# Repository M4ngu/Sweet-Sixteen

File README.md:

# Sweet-Sixteen
Eurorack module based in the [16n faderbank][16n-faderbank/16n]. 

## The following changes were made to the original hardware:

-The PCB layout has been made from scratch, so it's totally different, with 0603 passives instead of 0805.

-A power section has been added to work within the eurorack modular synth format, with diode protection and the option to power the Teensy with an internal 5V LDO or the eurorack 5V rail (selectable with a jumper on the back of the module). The voltage to feed the faders now comes from a dedicated voltage regulator, more stable and precise than most USB voltage sources.

-16 Inputs has been added. A "default voltage" is normalled to the input jacks, so when something is plugged in, that normalization is broken, being the incomming CV attenuated by the fader. This adition makes the module to work also as 16 attenuators, Cv to Midi, Cv to i2C...

-The op-amps circuit has been modiffied, being TL074s for the CV outs and MCP6004s for the circuit that prepares the voltages to be read by the Teensy. In this version the MCP6004 are powered with 3,3V & GND (instead of the original 5V), the rail-to-rail characteristic of those op-amps provides voltage protection to the Teensy. That is specially handy for the CV inputs, as any voltage plugged in, will be limited to 3,3v by the MCP6004s. Another important modification in this part of the circuit is the addition of negative voltage references and that now is a summing inverting gain circuit (for that reason the FLIP option in the firmware is necessary for this version of the hardware, as in the minimum position of the fader the voltage readed by the Teensy will be 3,3V and in the max position it will be 0V). The TL074s are powered by +12V & -12V.

-Four slide switches has been added to swap the voltage reference (1 for every 4 faders, there was no room for 16 switches). The reason is to allow negative voltages to be coorectly converted to midi CC (or i2C). In the normal position a 0V input is traduced as minimum CC value, with the switch turned up the voltage reference is -2,5V (instead of -5V) that means that 0V input correspond to the center position of the MidiCC, positive voltages will increase the value while negative ones will decrease it.

-The output voltage of the faders (that "default voltage" normalled to the jacks) has been increassed to 8v, the original 5v seems to be not enough to work in eurorack, like to wide open-close the cutoff of a filter etc. I decided to go 8v instead of 10v because of the CV inputs. If the circuit that prepares the voltages comming from the faders to be readed by the Teensy is expecting 10v then it will be impossible to cover all the range of a MidiCC with an LFO which is ±4v (or 8v pp). For the contrary, if that circuit is expecting 8V it can not only cover the whole Midi CC range but also allows saturating the waveform if the voltage source has over 8V pp (like a 10V envelope or a ±5V LFO).

-16 bicolor leds has been added in parallel with the CV out, allowing visual feedback of what's going on each track, specially handy when using the CV inputs.

-USB type B connector pcb mounted has been also added. Those connectors are much stronger than mini or micro ones, the USB 5V pin is not connected, this way you can update the firmware of the Teensy without powering off the module.

Various versions of the firmware are available, all them derived from the 16n by Tom Armitage.

Manual and build guide:

https://www.tesseractmodular.com/manuals/sweet-sixteen-manual

## [firmware](firmware/)

## [hardware](hardware/)

### There are 16 faders/channels, which can be used as:

 -Midi controller.  
 -Manual CV generator (0 to 8v range).  
 -Attenuator.  
 -CV to Midi CC.  
 -i2C controller.  
 -CV to i2C data.  

### Features:

 -16 inputs.  
 -16 outputs.  
 -16 faders.  
 -16 bi-color leds to show what's going on in every channel.  
 -Midi trs out.  
 -Jumpers on the back to swap between 'Arturia/Novation'  and 'Korg/Makenoise' Midi trs standards.  
 -USB Midi out (connector type B, usb midi class compliant device).  
 -4 switches to enable bi-polar CV to Midi/i2C conversion (one for every 4 channels).  
 -i2C via mini jack on front panel and pin header on the back of the module.  

## Credits
This is a derivative work of the [16n faderbank][16n-faderbank/16n].  
Based on original work by [Brian Crabtree][tehn] and Sean Hellfritsch.  
Minijack MIDI, I2C circuitry and CV outputs by [Tom Armitage][infovore].  
Firmware by [Brian Crabtree][tehn], [Tom Armitage][infovore], and [Brendon Cassidy][bpcmusic].  
Eurorack conversion, hardware & firmware mods by Mangu Díaz 2019.  

## Licensing

Panels and electronic schematics/layouts/gerber files are licensed under
[Creative Commons Attribution Share-Alike 4.0][ccbysa].

Firmware is licensed under the [MIT License][mitlicense].

[linespost]: https://llllllll.co/t/sixteen-n-faderbank/3643
[tehn]: https://github.com/tehn
[bpcmusic]: https://github.com/bpcmusic
[infovore]: https://github.com/infovore
[octobom]: https://octopart.com/bom-tool/unJxkzvR
[ccbysa]: https://creativecommons.org/licenses/by-sa/4.0/
[mitlicense]: https://opensource.org/licenses/MIT
[16n-faderbank/16n]: https://github.com/16n-faderbank/16n

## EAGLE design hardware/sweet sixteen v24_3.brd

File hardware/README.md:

If you want to order pcbs yourself make sure you have a valid replacement for the faders, the ones I use may have a weird pinout. You can also edit the board in order to use your desired fader model.

The voltage of the faders (when there's nothing plugged in) could be easy modified by replacing the IC4 for another LDO and changing the value of the summing resistors in the MCP6004 circuits, in order to get 3,3v (or close) from the LDO once passes throught the op-amp.

The formula is pretty simple: 

Vin * (RFB / RIN) = 3,3 

In this case the IC4 LDO is an 8V regulator, so: 

8v * (33k / 80,6k) = 3,27v

Keep in mind that if you change the 33k feedback resistor for other value, the summing resistors for the voltage reference must be also adapted with the same criteria: 

5v * (33k / 49,9k) = 3,3v

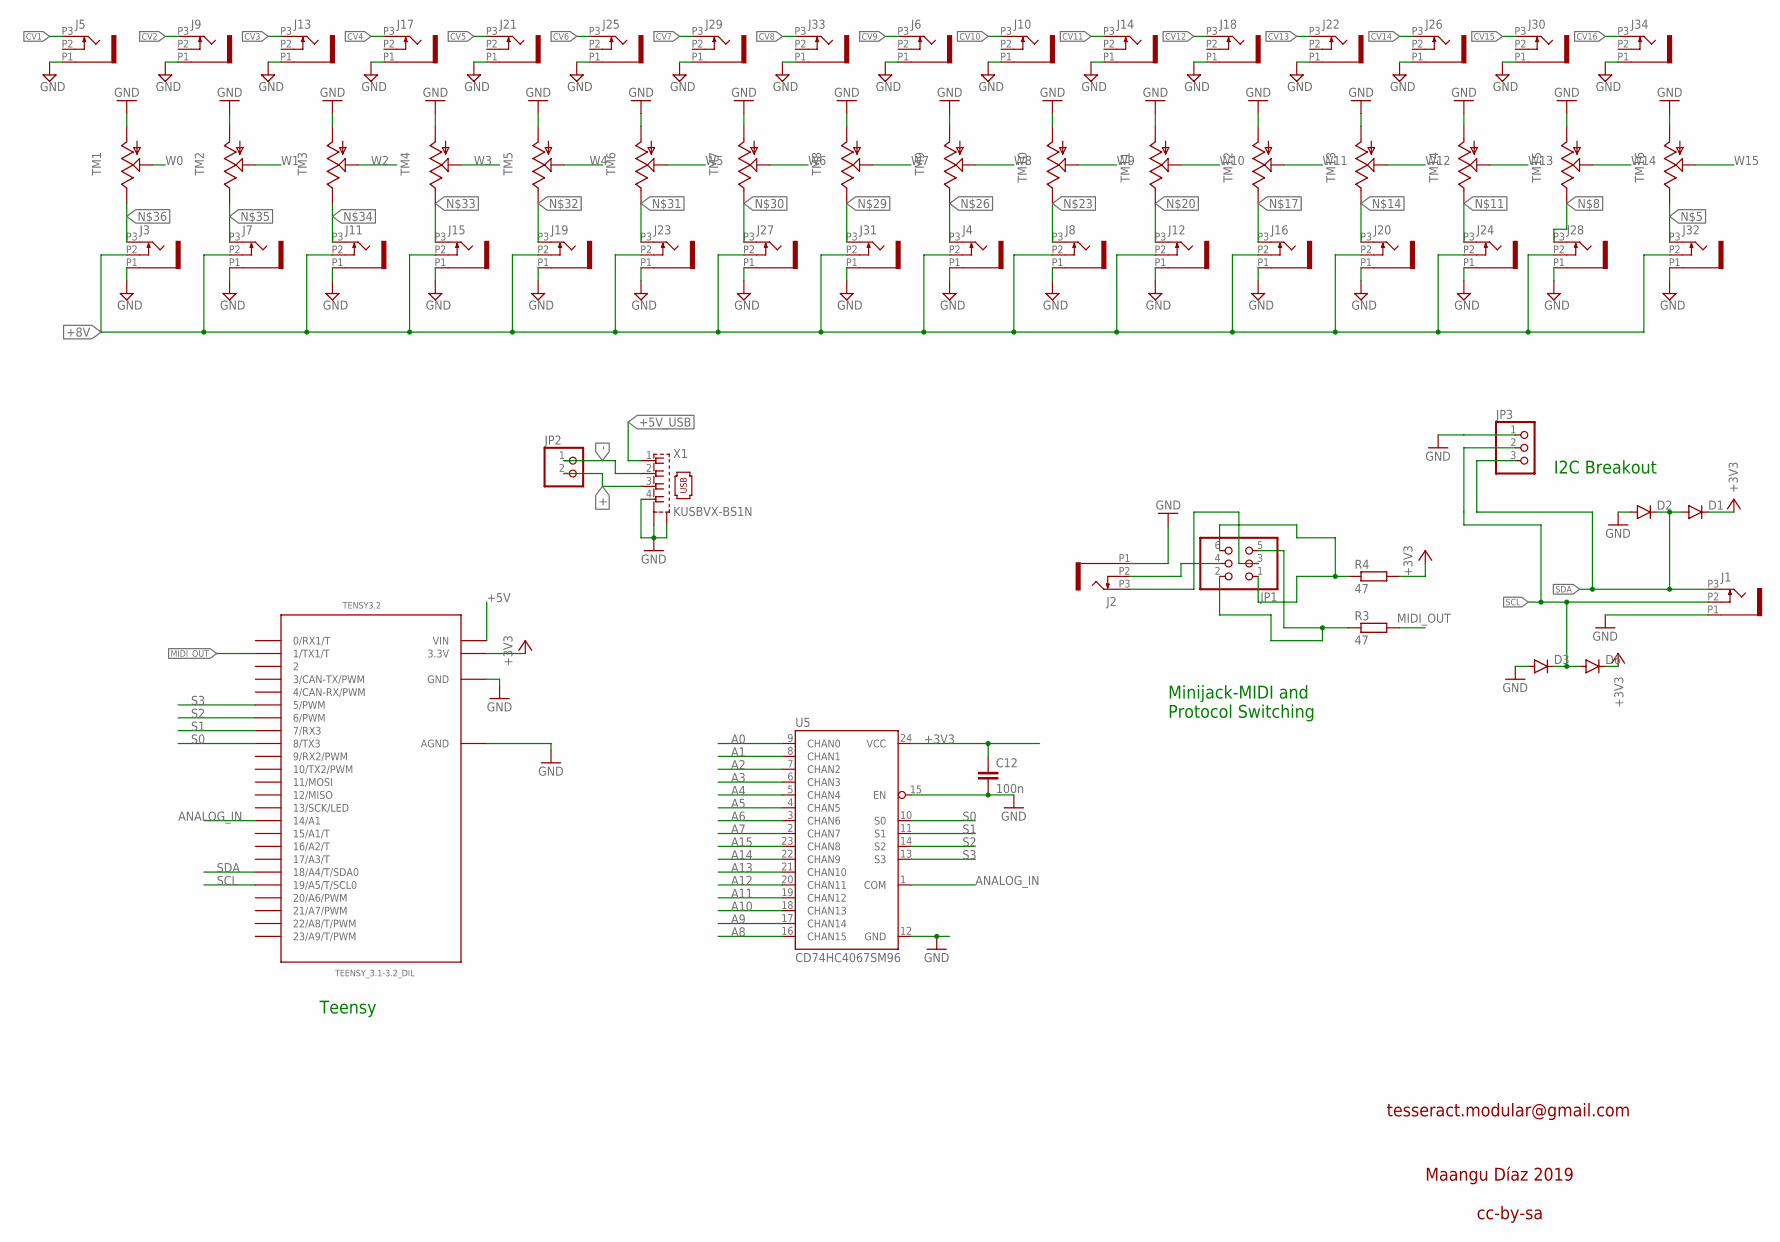
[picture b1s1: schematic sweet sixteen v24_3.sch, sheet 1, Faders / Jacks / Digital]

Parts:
C12: 100n; C0603
D1, D2, D3, D6: DIODESOD123; SOD-123
J1, J2, J3, J4, J5, J6, J7, J8, J9, J10, J11, J12, J13, J14, J15, J16, J17, J18, J19, J20, J21, J22, J23, J24, J25, J26, J27, J28, J29, J30, J31, J32, J33, J34: PJ301_THONKICONN6; WQP_PJ_301M6
JP1: PINHD-2X3; 2X03
JP2: PINHD-1X2; 1X02
JP3: PINHD-1X3; 1X03
R3, R4: 47; R0805
TENSY3.2: TEENSY_3.1-3.2_DIL; TEENSY_3.0-3.2&LC_DIL
TM1, TM2, TM3, TM4, TM5, TM6, TM7, TM8, TM9, TM10, TM11, TM12, TM13, TM14, TM15, TM16: TRIMSLIDE45; SLIDEPOT-45
U5: CD74HC4067SM96; SOIC127P1030X265-24
X1: KUSBVX-BS1N

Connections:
+: JP2.2, X1.3
+3V3: C12.1, D1.C, D6.C, R4.2, TENSY3.2.3.3V, U5.24 (VCC); also elsewhere on the board
+5V: TENSY3.2.VIN; also elsewhere on the board
+5V_USB: X1.1
+8V: J3.P2 (2), J4.P2 (2), J7.P2 (2), J8.P2 (2), J11.P2 (2), J12.P2 (2), J15.P2 (2), J16.P2 (2), J19.P2 (2), J20.P2 (2), J23.P2 (2), J24.P2 (2), J27.P2 (2), J28.P2 (2), J31.P2 (2), J32.P2 (2); also elsewhere on the board
-: JP2.1, X1.2
A0: U5.9 (CHAN0); also elsewhere on the board
A1: U5.8 (CHAN1); also elsewhere on the board
A2: U5.7 (CHAN2); also elsewhere on the board
A3: U5.6 (CHAN3); also elsewhere on the board
A4: U5.5 (CHAN4); also elsewhere on the board
A5: U5.4 (CHAN5); also elsewhere on the board
A6: U5.3 (CHAN6); also elsewhere on the board
A7: U5.2 (CHAN7); also elsewhere on the board
A8: U5.16 (CHAN15); also elsewhere on the board
A9: U5.17 (CHAN14); also elsewhere on the board
A10: U5.18 (CHAN13); also elsewhere on the board
A11: U5.19 (CHAN12); also elsewhere on the board
A12: U5.20 (CHAN11); also elsewhere on the board
A13: U5.21 (CHAN10); also elsewhere on the board
A14: U5.22 (CHAN9); also elsewhere on the board
A15: U5.23 (CHAN8); also elsewhere on the board
ANALOG_IN: TENSY3.2.14/A0 (14/A1), U5.1 (COM)
CV1: J5.P3 (3); also elsewhere on the board
CV2: J9.P3 (3); also elsewhere on the board
CV3: J13.P3 (3); also elsewhere on the board
CV4: J17.P3 (3); also elsewhere on the board
CV5: J21.P3 (3); also elsewhere on the board
CV6: J25.P3 (3); also elsewhere on the board
CV7: J29.P3 (3); also elsewhere on the board
CV8: J33.P3 (3); also elsewhere on the board
CV9: J6.P3 (3); also elsewhere on the board
CV10: J10.P3 (3); also elsewhere on the board
CV11: J14.P3 (3); also elsewhere on the board
CV12: J18.P3 (3); also elsewhere on the board
CV13: J22.P3 (3); also elsewhere on the board
CV14: J26.P3 (3); also elsewhere on the board
CV15: J30.P3 (3); also elsewhere on the board
CV16: J34.P3 (3); also elsewhere on the board
GND: C12.2, D2.A, D3.A, J1.P1 (1), J2.P1 (1), J3.P1 (1), J4.P1 (1), J5.P1 (1), J6.P1 (1), J7.P1 (1), J8.P1 (1), J9.P1 (1), J10.P1 (1), J11.P1 (1), J12.P1 (1), J13.P1 (1), J14.P1 (1), J15.P1 (1), J16.P1 (1), J17.P1 (1), J18.P1 (1), J19.P1 (1), J20.P1 (1), J21.P1 (1), J22.P1 (1), J23.P1 (1), J24.P1 (1), J25.P1 (1), J26.P1 (1), J27.P1 (1), J28.P1 (1), J29.P1 (1), J30.P1 (1), J31.P1 (1), J32.P1 (1), J33.P1 (1), J34.P1 (1), JP3.1, TENSY3.2.AGND, TENSY3.2.GND, TM1.A, TM2.A, TM3.A, TM4.A, TM5.A, TM6.A, TM7.A, TM8.A, TM9.A, TM10.A, TM11.A, TM12.A, TM13.A, TM14.A, TM15.A, TM16.A, U5.12 (GND), U5.15 (EN), X1.4, X1.M1 (S1), X1.M2 (S2); also elsewhere on the board
MIDI_OUT: R3.2, TENSY3.2.1 (1/TX1/T)
unnamed: J2.P3 (3), JP1.3
unnamed: J2.P2 (2), JP1.4
unnamed: JP1.2, JP1.5, R3.1
unnamed: JP1.1, JP1.6, R4.1
unnamed: J32.P3 (3), TM16.B
unnamed: J28.P3 (3), TM15.B
unnamed: J24.P3 (3), TM14.B
unnamed: J20.P3 (3), TM13.B
unnamed: J16.P3 (3), TM12.B
unnamed: J12.P3 (3), TM11.B
unnamed: J8.P3 (3), TM10.B
unnamed: J4.P3 (3), TM9.B
unnamed: J31.P3 (3), TM8.B
unnamed: J27.P3 (3), TM7.B
unnamed: J23.P3 (3), TM6.B
unnamed: J19.P3 (3), TM5.B
unnamed: J15.P3 (3), TM4.B
unnamed: J11.P3 (3), TM3.B
unnamed: J7.P3 (3), TM2.B
unnamed: J3.P3 (3), TM1.B
S0: TENSY3.2.8 (8/TX3), U5.10 (S0)
S1: TENSY3.2.7 (7/RX3), U5.11 (S1)
S2: TENSY3.2.6 (6/PWM), U5.14 (S2)
S3: TENSY3.2.5 (5/PWM), U5.13 (S3)
SCL: D3.C, D6.A, J1.P2 (2), JP3.2, TENSY3.2.19/A5 (19/A5/T/SCL0)
SDA: D1.A, D2.C, J1.P3 (3), JP3.3, TENSY3.2.18/A4 (18/A4/T/SDA0)
W0: TM1.WIPER; also elsewhere on the board
W1: TM2.WIPER; also elsewhere on the board
W2: TM3.WIPER; also elsewhere on the board
W3: TM4.WIPER; also elsewhere on the board
W4: TM5.WIPER; also elsewhere on the board
W5: TM6.WIPER; also elsewhere on the board
W6: TM7.WIPER; also elsewhere on the board
W7: TM8.WIPER; also elsewhere on the board
W8: TM9.WIPER; also elsewhere on the board
W9: TM10.WIPER; also elsewhere on the board
W10: TM11.WIPER; also elsewhere on the board
W11: TM12.WIPER; also elsewhere on the board
W12: TM13.WIPER; also elsewhere on the board
W13: TM14.WIPER; also elsewhere on the board
W14: TM15.WIPER; also elsewhere on the board
W15: TM16.WIPER; also elsewhere on the board

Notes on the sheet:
Teensy
Minijack-MIDI and Protocol Switching
I2C Breakout
cc-by-sa
Maangu Díaz 2019
tesseract.modular@gmail.com

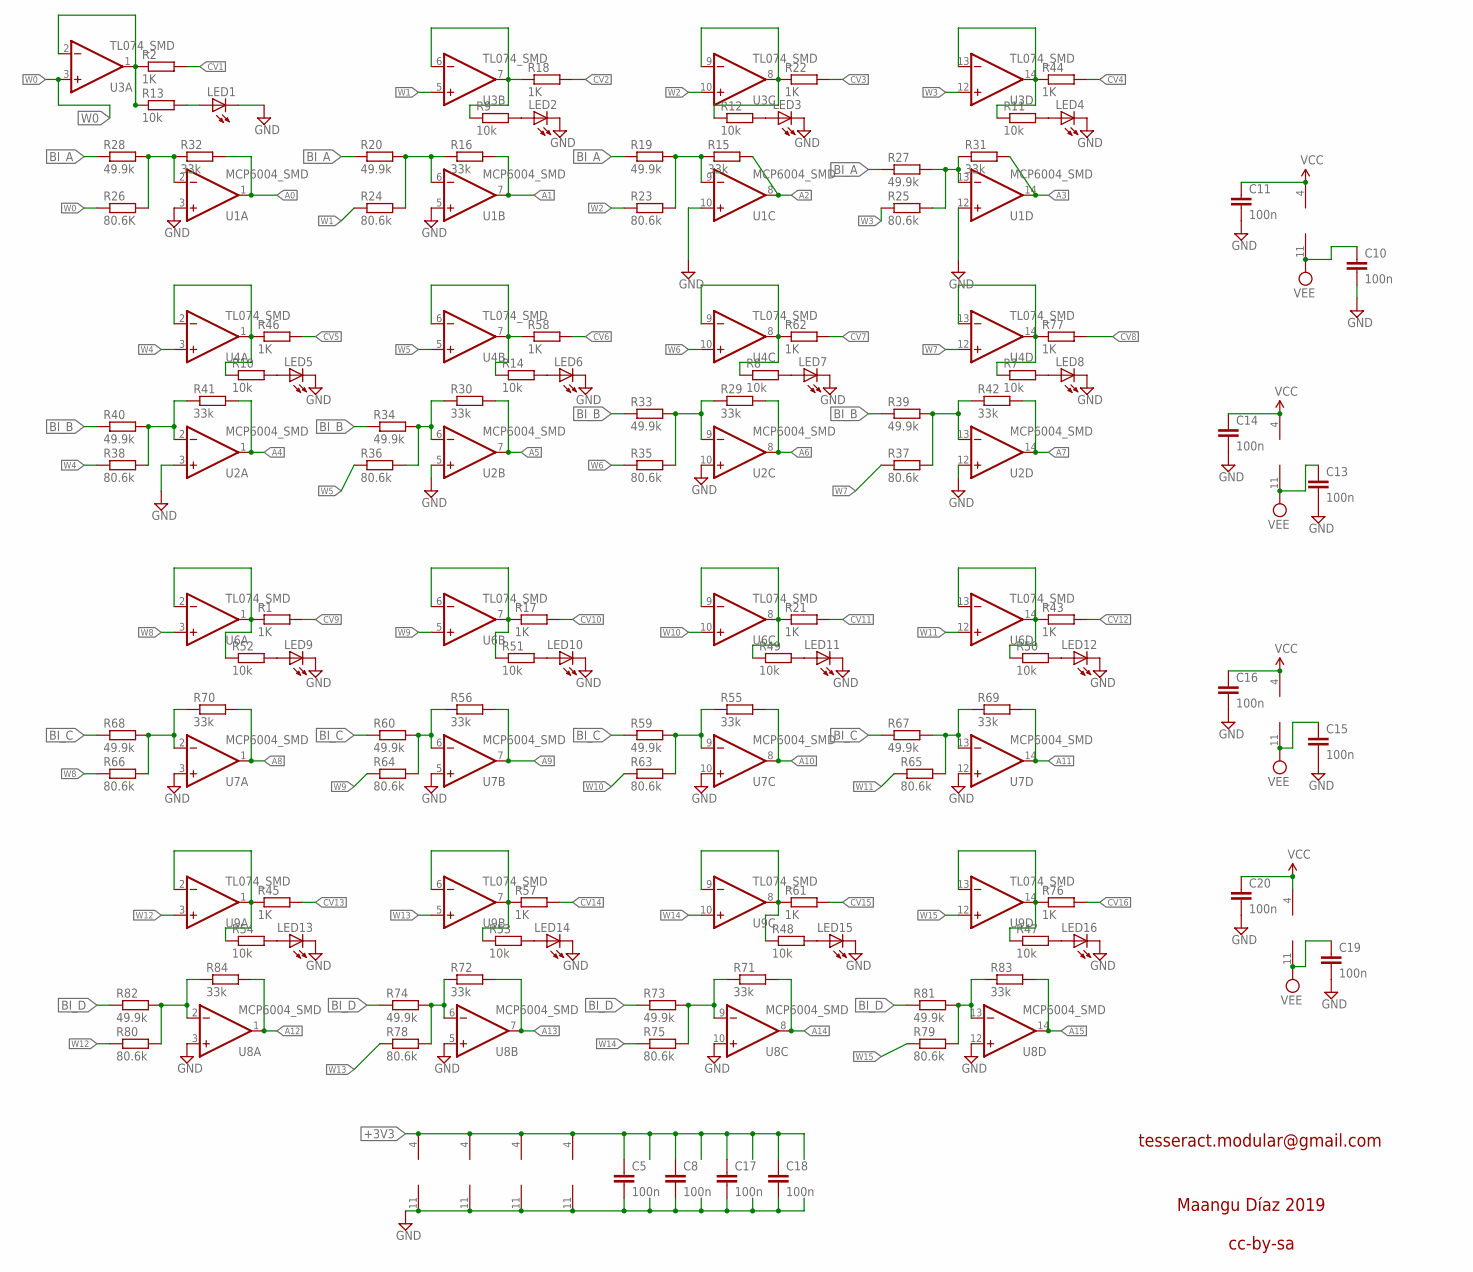
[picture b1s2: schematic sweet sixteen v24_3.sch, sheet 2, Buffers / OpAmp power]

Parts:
C5, C10, C11, C13, C14, C15, C16, C18, C19, C20: 100n; C0603
C8, C17: 100n; C0603K
LED1, LED2, LED3, LED4, LED5, LED6, LED7, LED8, LED9, LED10, LED11, LED12, LED13, LED14, LED15, LED16: LED3MM
R1, R2, R17, R18, R21, R22, R43, R44, R45, R46, R57, R58, R61, R62, R76, R77: 1K; R0603
R7, R8, R9, R10, R11, R12, R13, R14, R47, R48, R49, R50, R51, R52, R53, R54: 10k; R0603
R15, R16, R29, R30, R31, R32, R41, R42, R55, R56, R69, R70, R71, R72, R83, R84: 33k; R0603
R19, R20, R27, R28, R33, R34, R39, R40, R59, R60, R67, R68, R73, R74, R81, R82: 49.9k; R0603
R23, R24, R25, R35, R36, R37, R38, R63, R64, R65, R66, R75, R78, R79, R80: 80.6k; R0603
R26: 80.6K; R0603
U1, U2, U7, U8: MCP6004_SMD; SO14
U3, U4, U6, U9: TL074_SMD; SO14

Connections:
+3V3: C5.1, C8.1, C17.1, C18.1, U1.4 (V+), U2.4 (V+), U7.4 (V+), U8.4 (V+); also elsewhere on the board
A0: R32.2, U1.1 (OUT); also elsewhere on the board
A1: R16.2, U1.7 (OUT); also elsewhere on the board
A2: R15.2, U1.8 (OUT); also elsewhere on the board
A3: R31.2, U1.14 (OUT); also elsewhere on the board
A4: R41.2, U2.1 (OUT); also elsewhere on the board
A5: R30.2, U2.7 (OUT); also elsewhere on the board
A6: R29.2, U2.8 (OUT); also elsewhere on the board
A7: R42.2, U2.14 (OUT); also elsewhere on the board
A8: R70.2, U7.1 (OUT); also elsewhere on the board
A9: R56.2, U7.7 (OUT); also elsewhere on the board
A10: R55.2, U7.8 (OUT); also elsewhere on the board
A11: R69.2, U7.14 (OUT); also elsewhere on the board
A12: R84.2, U8.1 (OUT); also elsewhere on the board
A13: R72.2, U8.7 (OUT); also elsewhere on the board
A14: R71.2, U8.8 (OUT); also elsewhere on the board
A15: R83.2, U8.14 (OUT); also elsewhere on the board
BI_A: R19.1, R20.1, R27.1, R28.1; also elsewhere on the board
BI_B: R33.1, R34.1, R39.1, R40.1; also elsewhere on the board
BI_C: R59.1, R60.1, R67.1, R68.1; also elsewhere on the board
BI_D: R73.1, R74.1, R81.1, R82.1; also elsewhere on the board
CV1: R2.2; also elsewhere on the board
CV2: R18.2; also elsewhere on the board
CV3: R22.2; also elsewhere on the board
CV4: R44.2; also elsewhere on the board
CV5: R46.2; also elsewhere on the board
CV6: R58.2; also elsewhere on the board
CV7: R62.2; also elsewhere on the board
CV8: R77.2; also elsewhere on the board
CV9: R1.2; also elsewhere on the board
CV10: R17.2; also elsewhere on the board
CV11: R21.2; also elsewhere on the board
CV12: R43.2; also elsewhere on the board
CV13: R45.2; also elsewhere on the board
CV14: R57.2; also elsewhere on the board
CV15: R61.2; also elsewhere on the board
CV16: R76.2; also elsewhere on the board
GND: C5.2, C8.2, C10.2, C11.2, C13.2, C14.2, C15.2, C16.2, C17.2, C18.2, C19.2, C20.2, LED1.K (C), LED2.K (C), LED3.K (C), LED4.K (C), LED5.K (C), LED6.K (C), LED7.K (C), LED8.K (C), LED9.K (C), LED10.K (C), LED11.K (C), LED12.K (C), LED13.K (C), LED14.K (C), LED15.K (C), LED16.K (C), U1.3 (+IN), U1.5 (+IN), U1.10 (+IN), U1.11 (V-), U1.12 (+IN), U2.3 (+IN), U2.5 (+IN), U2.10 (+IN), U2.11 (V-), U2.12 (+IN), U7.3 (+IN), U7.5 (+IN), U7.10 (+IN), U7.11 (V-), U7.12 (+IN), U8.3 (+IN), U8.5 (+IN), U8.10 (+IN), U8.11 (V-), U8.12 (+IN); also elsewhere on the board
unnamed: R15.1, R19.2, R23.2, U1.9 (-IN)
unnamed: R25.2, R27.2, R31.1, U1.13 (-IN)
unnamed: R26.2, R28.2, R32.1, U1.2 (-IN)
unnamed: R16.1, R20.2, R24.2, U1.6 (-IN)
unnamed: R38.2, R40.2, R41.1, U2.2 (-IN)
unnamed: R30.1, R34.2, R36.2, U2.6 (-IN)
unnamed: R29.1, R33.2, R35.2, U2.9 (-IN)
unnamed: R37.2, R39.2, R42.1, U2.13 (-IN)
unnamed: R80.2, R82.2, R84.1, U8.2 (-IN)
unnamed: LED1.A, R13.2
unnamed: R71.1, R73.2, R75.2, U8.9 (-IN)
unnamed: R79.2, R81.2, R83.1, U8.13 (-IN)
unnamed: R66.2, R68.2, R70.1, U7.2 (-IN)
unnamed: LED2.A, R9.2
unnamed: R56.1, R60.2, R64.2, U7.6 (-IN)
unnamed: R55.1, R59.2, R63.2, U7.9 (-IN)
unnamed: R65.2, R67.2, R69.1, U7.13 (-IN)
unnamed: LED3.A, R12.2
unnamed: LED4.A, R11.2
unnamed: LED8.A, R7.2
unnamed: LED7.A, R8.2
unnamed: LED6.A, R14.2
unnamed: LED5.A, R10.2
unnamed: LED9.A, R52.2
unnamed: LED10.A, R51.2
unnamed: LED11.A, R49.2
unnamed: LED12.A, R50.2
unnamed: LED13.A, R54.2
unnamed: LED14.A, R53.2
unnamed: LED15.A, R48.2
unnamed: R72.1, R74.2, R78.2, U8.6 (-IN)
unnamed: LED16.A, R47.2
unnamed: R2.1, R13.1, U3.1 (OUT), U3.2 (-IN)
unnamed: R9.1, R18.1, U3.6 (-IN), U3.7 (OUT)
unnamed: R12.1, R22.1, U3.8 (OUT), U3.9 (-IN)
unnamed: R11.1, R44.1, U3.13 (-IN), U3.14 (OUT)
unnamed: R10.1, R46.1, U4.1 (OUT), U4.2 (-IN)
unnamed: R14.1, R58.1, U4.6 (-IN), U4.7 (OUT)
unnamed: R8.1, R62.1, U4.8 (OUT), U4.9 (-IN)
unnamed: R7.1, R77.1, U4.13 (-IN), U4.14 (OUT)
unnamed: R1.1, R52.1, U6.1 (OUT), U6.2 (-IN)
unnamed: R17.1, R51.1, U6.6 (-IN), U6.7 (OUT)
unnamed: R21.1, R49.1, U6.8 (OUT), U6.9 (-IN)
unnamed: R43.1, R50.1, U6.13 (-IN), U6.14 (OUT)
unnamed: R45.1, R54.1, U9.1 (OUT), U9.2 (-IN)
unnamed: R53.1, R57.1, U9.6 (-IN), U9.7 (OUT)
unnamed: R48.1, R61.1, U9.8 (OUT), U9.9 (-IN)
unnamed: R47.1, R76.1, U9.13 (-IN), U9.14 (OUT)
VCC: C11.1, C14.1, C16.1, C20.1, U3.4 (V+), U4.4 (V+), U6.4 (V+), U9.4 (V+); also elsewhere on the board
VEE: C10.1, C13.1, C15.1, C19.1, U3.11 (V-), U4.11 (V-), U6.11 (V-), U9.11 (V-); also elsewhere on the board
W0: R26.1, U3.3 (+IN); also elsewhere on the board
W1: R24.1, U3.5 (+IN); also elsewhere on the board
W2: R23.1, U3.10 (+IN); also elsewhere on the board
W3: R25.1, U3.12 (+IN); also elsewhere on the board
W4: R38.1, U4.3 (+IN); also elsewhere on the board
W5: R36.1, U4.5 (+IN); also elsewhere on the board
W6: R35.1, U4.10 (+IN); also elsewhere on the board
W7: R37.1, U4.12 (+IN); also elsewhere on the board
W8: R66.1, U6.3 (+IN); also elsewhere on the board
W9: R64.1, U6.5 (+IN); also elsewhere on the board
W10: R63.1, U6.10 (+IN); also elsewhere on the board
W11: R65.1, U6.12 (+IN); also elsewhere on the board
W12: R80.1, U9.3 (+IN); also elsewhere on the board
W13: R78.1, U9.5 (+IN); also elsewhere on the board
W14: R75.1, U9.10 (+IN); also elsewhere on the board
W15: R79.1, U9.12 (+IN); also elsewhere on the board

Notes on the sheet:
cc-by-sa
Maangu Díaz 2019
tesseract.modular@gmail.com

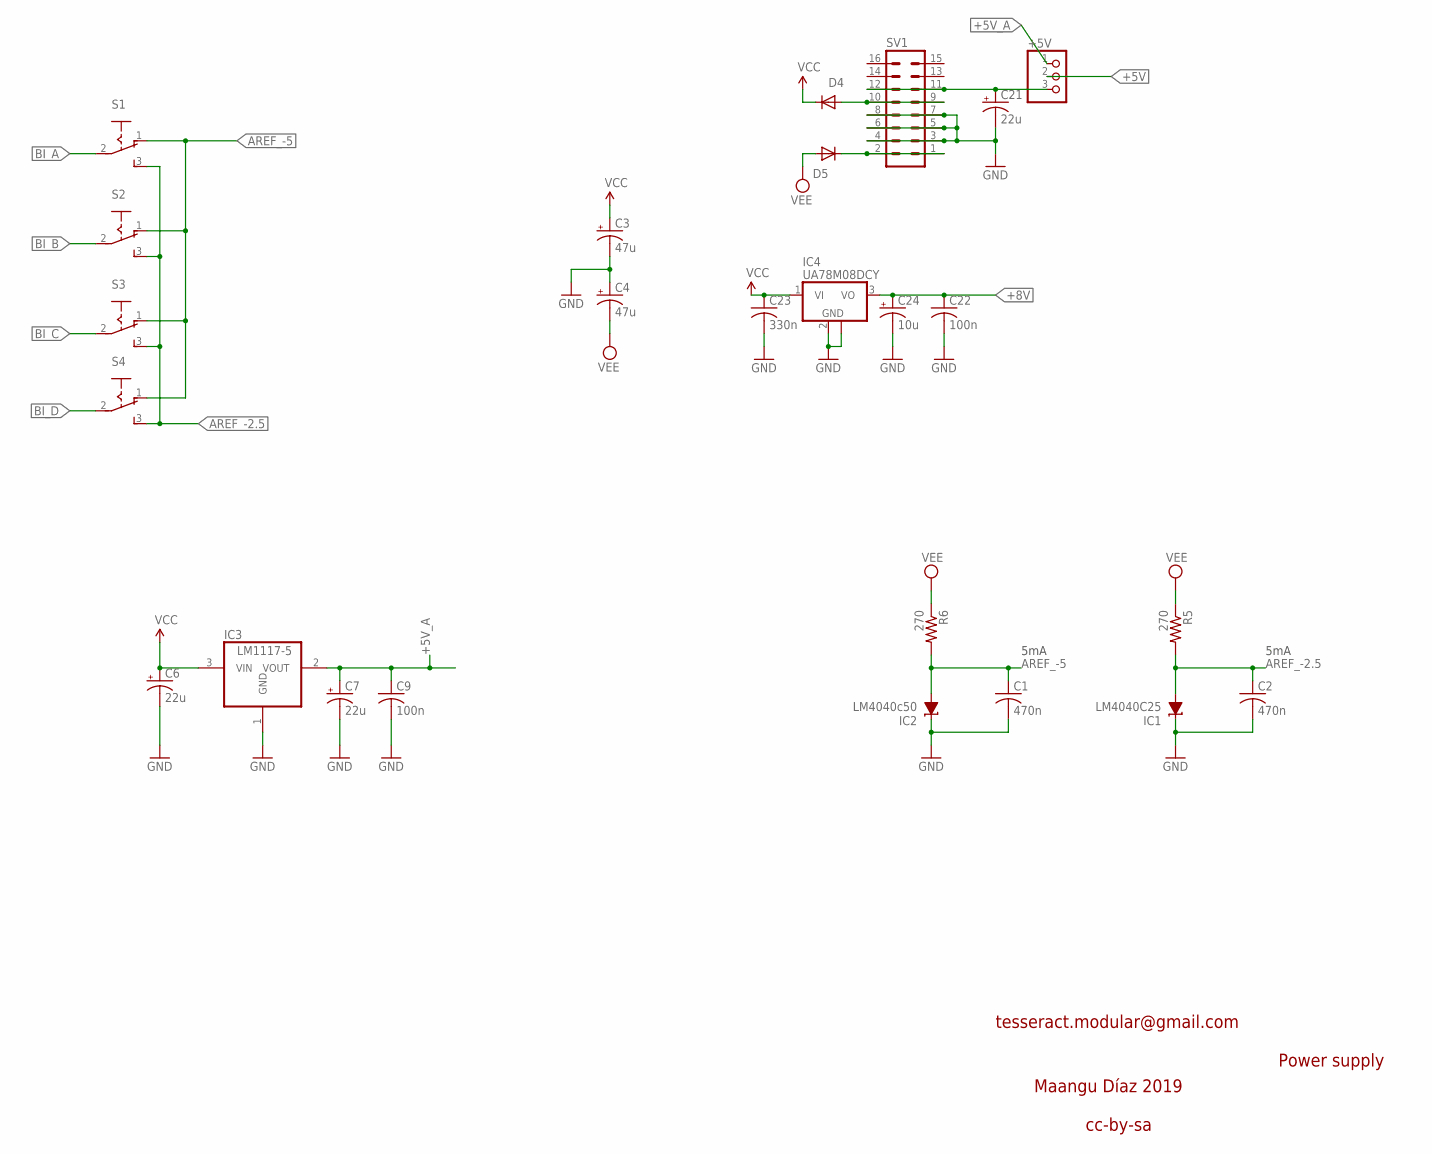
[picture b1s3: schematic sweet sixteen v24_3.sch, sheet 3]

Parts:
+5V: PINHD-1X3; 1X03
C1, C2: 470n; C0603
C3, C4: 47u; PANASONIC_D
C6, C7, C21: 22u; PANASONIC_D
C9, C22: 100n; C0603
C23: 330n; C0603
C24: 10u; PANASONIC_C
D4, D5: 1N5819HW; SOD123
IC1: LM4040C25; DBZ_R-PDSO-G3
IC2: LM4040c50; DBZ_R-PDSO-G3
IC3: LM1117-5; SOT223
IC4: UA78M08DCY; SOT223
R5, R6: 270; R0603
S1, S2, S3, S4: 255SB-MANGURRIN; 255SB_MANGU
SV1: ML16

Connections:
+5V: +5V.2; also elsewhere on the board
+5V_A: +5V.1, C7.+, C9.1, IC3.2 (VOUT)
+8V: C22.1, C24.+, IC4.3 (VO); also elsewhere on the board
AREF_-2.5: C2.1, IC1.2 (A), R5.2, S1.3 (S), S2.3 (S), S3.3 (S), S4.3 (S)
AREF_-5: C1.1, IC2.2 (A), R6.2, S1.1 (O), S2.1 (O), S3.1 (O), S4.1 (O)
BI_A: S1.2; also elsewhere on the board
BI_B: S2.2; also elsewhere on the board
BI_C: S3.2; also elsewhere on the board
BI_D: S4.2; also elsewhere on the board
GND: C1.2, C2.2, C3.-, C4.+, C6.-, C7.-, C9.2, C21.-, C22.2, C23.2, C24.-, IC1.1 (C), IC2.1 (C), IC3.1 (GND), IC4.2 (GND), IC4.4 (GND), SV1.3, SV1.4, SV1.5, SV1.6, SV1.7, SV1.8; also elsewhere on the board
unnamed: +5V.3, C21.+, SV1.11, SV1.12
unnamed: D4.A, SV1.9, SV1.10
unnamed: D5.C, SV1.1, SV1.2
VCC: C3.+, C6.+, C23.1, D4.C, IC3.3 (VIN), IC4.1 (VI); also elsewhere on the board
VEE: C4.-, D5.A, R5.1, R6.1; also elsewhere on the board

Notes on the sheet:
cc-by-sa
Maangu Díaz 2019
tesseract.modular@gmail.com
Power supply
5mA

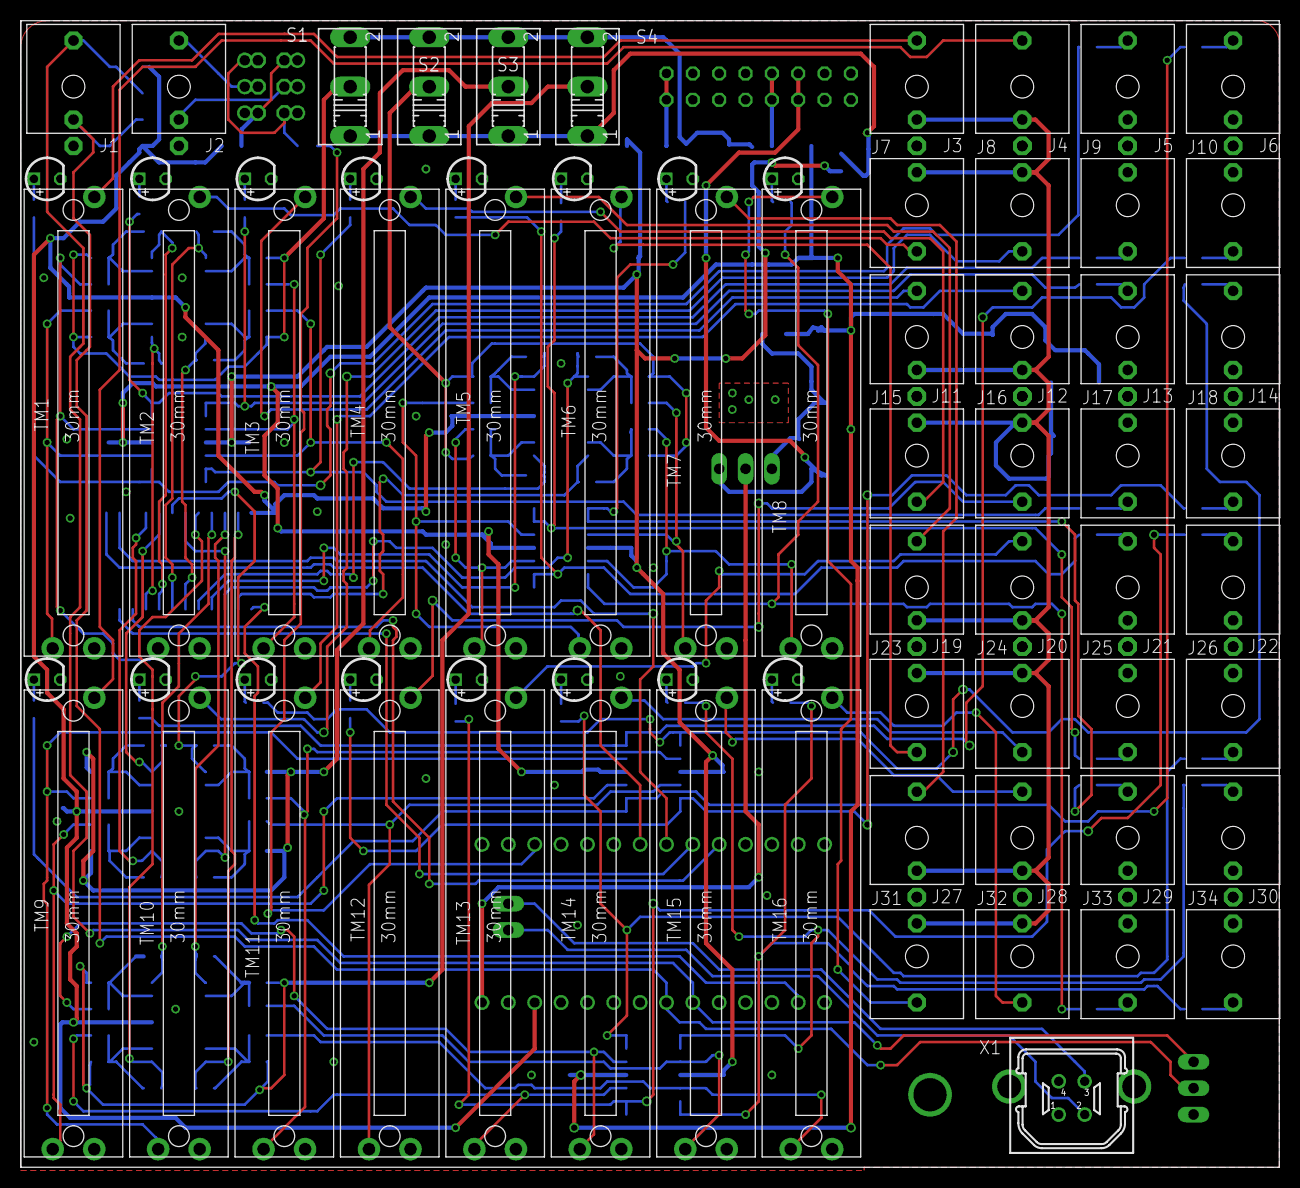
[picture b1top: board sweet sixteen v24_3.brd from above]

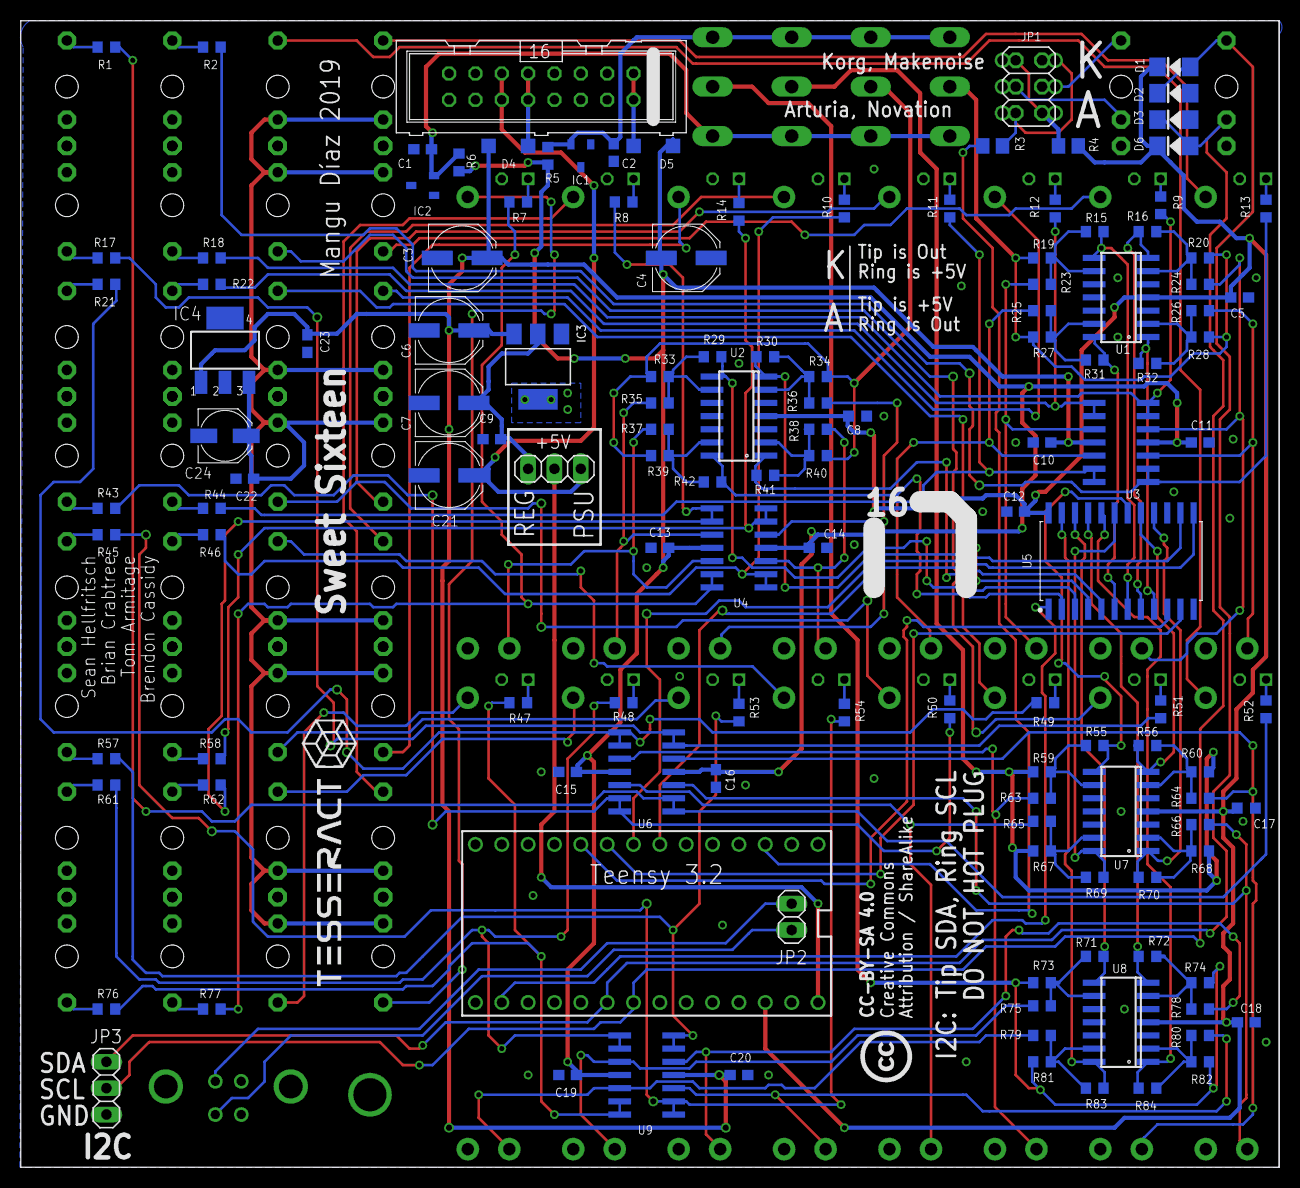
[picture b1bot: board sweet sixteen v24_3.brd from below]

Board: 2 copper layers, 121.3 x 110.5 mm, 205 parts (133 on the bottom side), 142 nets.

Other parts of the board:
U$1: LOGO

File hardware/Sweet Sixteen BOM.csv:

Qty,DESIGNATOR,FOOTPRINT,COMMENT,Description,MF
2,"R3, R4",0805-R,47,"RESISTOR, European symbol",
2,"R5, R6",0603-R,270,"RESISTOR, American symbol",
16,"R1, R2, R17, R18, R21, R22, R43, R44, R45, R46, R57, R58, R61, R62, R76, R77",0603-R,1K,"RESISTOR, European symbol",
16,"R7, R8, R9, R10, R11, R12, R13, R14, R47, R48, R49, R50, R51, R52, R53, R54",0603-R,10k,"RESISTOR, European symbol",
16,"R15, R16, R29, R30, R31, R32, R41, R42, R55, R56, R69, R70, R71, R72, R83, R84",0603-R,33k,"RESISTOR, European symbol",
16,"R19, R20, R27, R28, R33, R34, R39, R40, R59, R60, R67, R68, R73, R74, R81, R82",0603-R,49.9k,"RESISTOR, European symbol",
1,R26,0603-R,50K,"RESISTOR, European symbol",
15,"R23, R24, R25, R35, R36, R37, R38, R63, R64, R65, R66, R75, R78, R79, R80",0603-R,80.6k,"RESISTOR, European symbol",
11,"C5, C10, C11, C12, C13, C14, C15, C16, C18, C19, C20, C8, C17, C9, C22",0603-C,100n,"CAPACITOR, European symbol",
1,C23,0603-C,330n,"CAPACITOR, American symbol",
2,"C1, C2",0603-C,470n,"CAPACITOR, American symbol",
1,C24,PANASONIC_C,10u,"POLARIZED CAPACITOR, American symbol",
3,"C6, C7, C21",PANASONIC_D,22u,"POLARIZED CAPACITOR, American symbol",
2,"C3, C4",PANASONIC_D,47u,"POLARIZED CAPACITOR, American symbol",
4,"D1, D2, D3, D6",SOD-123,1N4148,,
2,"D4, D5",SOD123,1N5819,DIODE,
1,IC3,SOT223,LM1117-5,800mA and 1A Low Dropout (LDO) Positive Regulator,
1,IC1,DBZ_R-PDSO-G3,LM4040C25,PRECISION MICROPOWER SHUNT VOLTAGE REFERENCE,
1,IC2,DBZ_R-PDSO-G3,LM4040c50,PRECISION MICROPOWER SHUNT VOLTAGE REFERENCE,
1,IC4,SOT223,UA78M08DCY,8V POSITIVE-VOLTAGE REGULATORS,
1,U5,SOIC127P1030X265-24,CD74HC4067SM96,16-channel analog MUX,
4,"U1, U2, U7, U8",SO14,MCP6004_SMD,Generic Quad Op Amp,
4,"U3, U4, U6, U9",SO14,TL074_SMD,Generic Quad Op Amp,
,,,,,
1,TENSY3.2,TEENSY_3.0-3.2&LC_DIL,TEENSY_3.1-3.2_DIL,Teensy 3.1 or 3.2 in a DIL Layout.,
34,"J1, J2, J3, J4, J5, J6, J7, J8, J9, J10, J11, J12, J13, J14, J15, J16, J17, J18, J19, J20, J21, J22, J23, J24, J25, J26, J27, J28, J29, J30, J31, J32, J33, J34",WQP_PJ_301M6,PJ301_THONKICONN6,,
1,X1,KUSBVX-BS1N,KUSBVX-BS1N,"USB B-type Receptacle Vertical, 4 Position, Through Hole",
2,"+5V, JP3",1X03,,PIN HEADER,
1,JP1,2X03,,PIN HEADER,
16,"TM1, TM2, TM3, TM4, TM5, TM6, TM7, TM8, TM9, TM10, TM11, TM12, TM13, TM14, TM15, TM16",SLIDEPOT-45,,Sliding potentiometers,
4,"S1, S2, S3, S4",,,SLIDING SWITCH,
16,"LED1, LED2, LED3, LED4, LED5, LED6, LED7, LED8, LED9, LED10, LED11, LED12, LED13, LED14, LED15, LED16",LED3MM,,BI-COLOR LED,
1,SV1,ML16,,HARTING,

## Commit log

2020-02-29 Add files via upload
    in this version a boot-up delay time has been added to make it work with the ER-301, when using PitchBend in the USB out a different midi CC can be used in the midi TRS out (and vice versa) and it do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
2020-02-29 Add files via upload
    added bill of materials
2020-05-02 various bugs fixed
    -fixed error when compiling without the #master option
    -fixed the values being different in the i2c for the channels with PitchBend is selected as midi controller
    -code reduced and simplified
2020-06-14 Create . ...
2020-06-14 Create . ...
2020-06-14 Create _16n_faderbank_firmware_Sweet
2020-06-14 various firmwares added
2021-06-01 Sweet_3 firmware added
2021-06-01 hex file moved
2023-01-09 Update Sweet_3.ino
    Added Function to send GESS Trigger to ER-301 Teletype Trigger
2023-01-10 function to send usb midi data to er-301 over i2c
    Implement function so send midi data receved from usb midi in to er-301 over i2c.
    Midi channel 1-16 is mapped to ic2 channel 20-25 and gets midi cv as pitch and gate.

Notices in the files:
hardware/sweet sixteen v24_3.brd:
CC-BY-SA 4.0
